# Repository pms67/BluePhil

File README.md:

# BluePhil
 STM32-based development board with various sensors. Update from LittleBrain board. Now includes GPS module, SD card, and CAN transceiver.

Gerber and assembly files ready for order at JLCPCB: https://jlcpcb.com/RPH

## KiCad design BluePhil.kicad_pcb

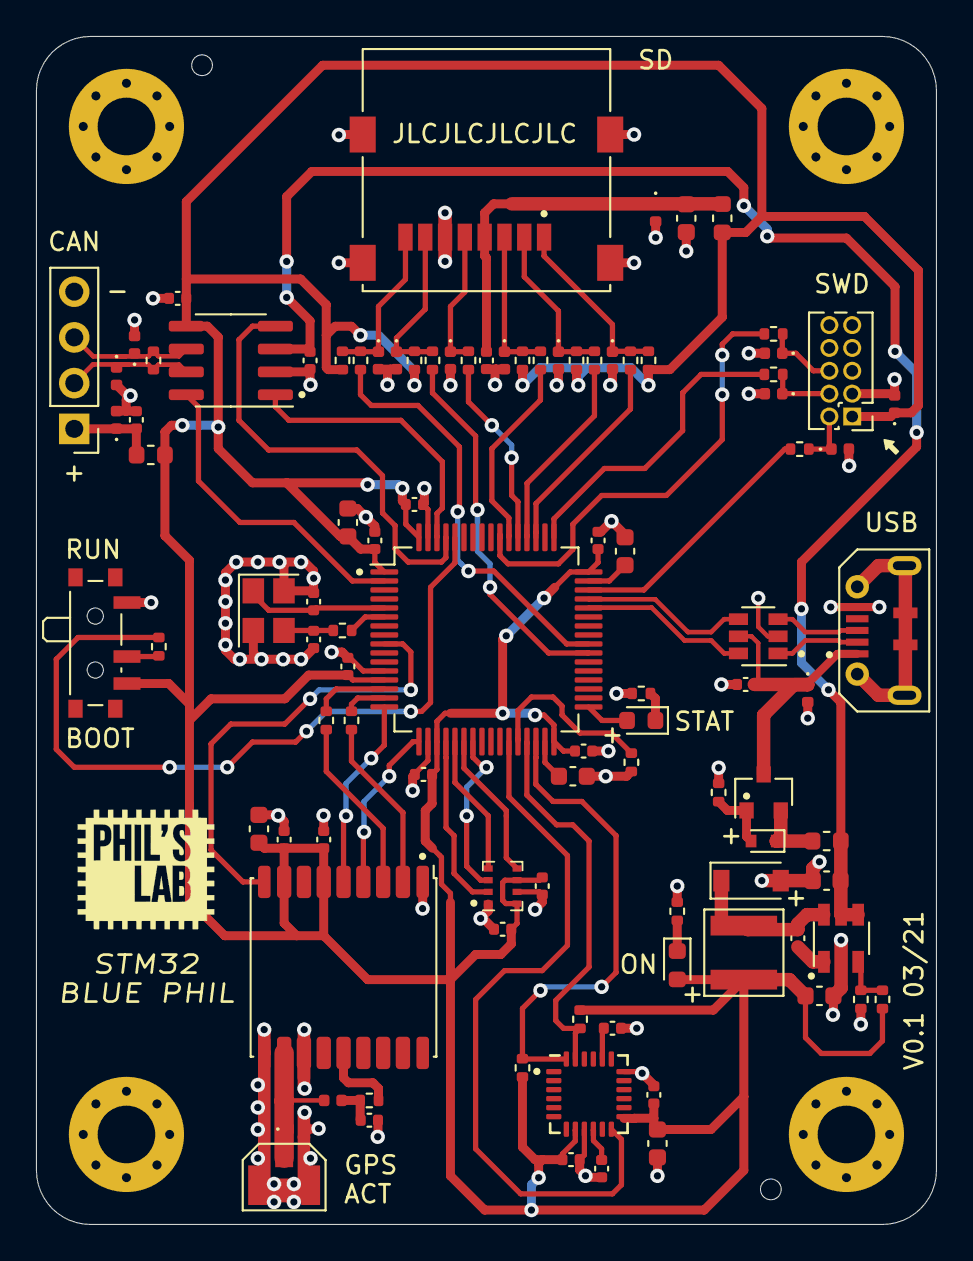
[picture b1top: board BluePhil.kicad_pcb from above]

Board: 2 copper layers, 50.0 x 66.0 mm, 103 parts (0 on the bottom side), 68 nets.

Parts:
C100, C207, C208: 2u2; C_0603_1608Metric
C101, C201, C202, C203, C204, C205, C206, C212, C301, C302, C400, C401, C403, C404, C405, C501, C502, C503, C504: 100n; C_0402_1005Metric
C102, C200, C300, C402, C500: 10u; C_0603_1608Metric
C209, C210: 10p; C_0402_1005Metric
C303: 10n; C_0402_1005Metric
C406: 2n2; C_0402_1005Metric
D100: LM5Z2V7T1G; D_SOD-523
D101: B5819W; D_SOD-123
D102: GREEN; LED_0603_1608Metric
D200: BLUE; LED_0603_1608Metric
D201, D202, D203, D204, D205, D300, D500, D501, D502, D503, D504, D505, D506, D507, D508, D509: RCLAMP0521P-N; D_0402_1005Metric
FB100, FB500, FB501: 100R; L_0603_1608Metric
H500, H501, H502, H503: MountingHole_Pad; MountingHole_3.2mm_M3_Pad_Via
J200: SWD; PinHeader_2x05_P1.27mm_Vertical
J201: USB_B_Micro; MicroXNJ
J300: U.FL; BWIPX-1-001E
J500: Micro_SD_Card; TF-102-15
J501: Conn_01x04; PinHeader_1x04_P2.54mm_Vertical
L1: 15u; MPIT4018-150M-LF
L300: 100n; L_0402_1005Metric
Q100: AO3401A; SOT-23
R100: 470R; R_0402_1005Metric
R101: 3k4; R_0402_1005Metric
R102: 1k02; R_0402_1005Metric
R103, R205: 1k; R_0402_1005Metric
R200, R202: 10k; R_0402_1005Metric
R201, R301, R302, R500, R501, R502, R503, R504, R505: 0R; R_0402_1005Metric
R203, R204: 2k2; R_0402_1005Metric
R206, R207, R208: 22R; R_0402_1005Metric
R300: 10R; R_0402_1005Metric
R506, R507, R508, R509, R510: 47k; R_0402_1005Metric
R511: 120R; R_0402_1005Metric
SW200: SW_SPDT; SW_SPDT_PCM12
U100: LM2842X; TSOT-23-6
U200: STM32F405RGT6; LQFP-64_10x10mm_P0.5mm
U201: USBLC6-2SC6; SOT-23-6
U300: MAX-M8Q; ublox_MAX
U400: SPL06-007; Bosch_LGA-8_2x2.5mm_P0.65mm_ClockwisePinNumbering
U401: MPU-6050; InvenSense_QFN-24_4x4mm_P0.5mm
U500: TJA1051T-3; SOIC-8_3.9x4.9mm_P1.27mm
Y200: 16MHz; Crystal_SMD_3225-4Pin_3.2x2.5mm

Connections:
+3V3: C102.1, C200.1, C201.1, C202.1, C203.1, C204.1, C205.1, C206.1, C300.1, C301.1, C302.1, C400.1, C401.1, C402.1, C403.1, C404.1, C503.2, D102.2, D201.1, FB500.2, FB501.2, J200.1, L1.2, R101.1, R203.1, R204.1, R506.1, R507.1, R508.1, R509.1, R510.1, SW200.3, U200.1, U200.13, U200.19, U200.32, U200.48, U200.64, U300.6, U300.8, U400.6, U400.8, U401.8, U401.13, U500.5
+5V: C100.1, C502.2, FB100.1, U100.4, U100.5, U500.3
/GPS/GPS_RX: R301.1, U300.3
/GPS/GPS_TX: R302.1, U300.2
/Microcontroller/CONN_SWCLK: D203.1, J200.4, R207.2
/Microcontroller/CONN_SWDIO: D204.1, J200.2, R206.2
/Microcontroller/CONN_SWO: D202.1, J200.6, R208.2
/Microcontroller/MCU_BOOT0: R200.1, U200.60
/Microcontroller/MCU_BOOT1: R202.1, U200.28
/Microcontroller/MCU_HSE_IN: C209.1, U200.5, Y200.1
/Microcontroller/MCU_HSE_OUT: R201.1, U200.6
/Microcontroller/MCU_HSE_OUT_R: C210.1, R201.2, Y200.3
/Microcontroller/MCU_LED_A: D200.2, U200.33
/Microcontroller/MCU_LED_K: D200.1, R205.1
/Microcontroller/MCU_VCAP1: C207.1, U200.31
/Microcontroller/MCU_VCAP2: C208.1, U200.47
/Microcontroller/SW_BOOT0: R200.2, SW200.2
/Miscellaneous/3V3_CAN: C504.1, D509.1, FB501.1, J501.1
/Miscellaneous/CAN+: D508.1, J501.2, R511.1, U500.7
/Miscellaneous/CAN-: D507.1, J501.3, R511.2, U500.6
/Miscellaneous/SD_CLK: D503.1, J500.5, R503.1
/Miscellaneous/SD_CMD: D502.1, J500.3, R502.1, R508.2
/Miscellaneous/SD_DAT0: D504.1, J500.7, R504.1, R507.2
/Miscellaneous/SD_DAT1: D505.1, J500.8, R505.1, R506.2
/Miscellaneous/SD_DAT2: D500.1, J500.1, R500.1, R510.2
/Miscellaneous/SD_DAT3: D501.1, J500.2, R501.1, R509.2
/Miscellaneous/SD_VDD: C500.2, C501.2, D506.1, FB500.1, J500.4
/Sensors/IMU_CPOUT: C406.1, U401.20
/Sensors/IMU_REGOUT: C405.1, U401.10
CAN_SILENT: U200.2, U500.8
CONN_USB_D+: J201.3, U201.3
CONN_USB_D-: J201.2, U201.1
GND: C100.2, C102.2, C200.2, C201.2, C202.2, C203.2, C204.2, C205.2, C206.2, C207.2, C208.2, C209.2, C210.2, C212.1, C300.2, C301.2, C302.2, C303.2, C400.2, C401.2, C402.2, C403.2, C404.2, C405.2, C406.2, C500.1, C501.1, C502.1, C503.1, C504.2, D101.2, D201.2, D202.2, D203.2, D204.2, D205.2, D300.2, D500.2, D501.2, D502.2, D503.2, D504.2, D505.2, D506.2, D507.2, D508.2, D509.2, H500.1, H501.1, H502.1, H503.1, J200.3, J200.5, J200.9, J201.5, J300.2, J500.6, J500.9, J501.4, R100.2, R102.2, R103.2, R202.2, R205.2, SW200.1, U100.2, U200.12, U200.18, U200.63, U201.2, U300.1, U300.10, U300.12, U400.1, U400.7, U401.9, U401.18, U500.2, Y200.2, Y200.4
GPS_NRST: U200.9, U300.9
GPS_ONOFF: U200.16, U300.5
GPS_PPS: U200.17, U300.4
IMU_INTERRUPT: U200.27, U401.12
MCU_CAN1_RX: U200.61, U500.4
MCU_CAN1_TX: U200.62, U500.1
MCU_I2C2_SCL: R203.2, U200.29, U401.23
MCU_I2C2_SDA: R204.2, U200.30, U401.24
MCU_SDIO_CK: R503.2, U200.53
MCU_SDIO_CMD: R502.2, U200.54
MCU_SDIO_D0: R504.2, U200.39
MCU_SDIO_D1: R505.2, U200.40
MCU_SDIO_D2: R500.2, U200.51
MCU_SDIO_D3: R501.2, U200.52
MCU_SPI1_MISO: U200.22, U400.5
MCU_SPI1_MOSI: U200.23, U400.3
MCU_SPI1_NSS: U200.20, U400.2
MCU_SPI1_SCK: U200.21, U400.4
MCU_SWCLK: R207.1, U200.49
MCU_SWDIO: R206.1, U200.46
MCU_SWO: R208.1, U200.55
MCU_UART4_RX: R302.2, U200.15
MCU_UART4_TX: R301.2, U200.14
MCU_USB_D+: U200.45, U201.4
MCU_USB_D-: U200.44, U201.6
unnamed: C101.1, D101.1, L1.1, U100.6
unnamed: C101.2, U100.1
unnamed: C303.1, L300.1, R300.1
unnamed: D100.1, FB100.2, Q100.2
unnamed: D100.2, Q100.1, R100.1
unnamed: D102.1, R103.1
unnamed: D300.1, J300.1, L300.2, U300.11
unnamed: R101.2, R102.1, U100.3
unnamed: R300.2, U300.14
VBUS: C212.2, D205.1, J201.1, Q100.3, U201.5

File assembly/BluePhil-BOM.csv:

Designator,Quantity,Value,Footprint,LCSC Part #
C102 C200 C300 C402 C500 ,5,10u,Capacitor_SMD:C_0603_1608Metric,C19702
C101 C201 C202 C203 C204 C205 C206 C212 C301 C302 C400 C401 C403 C404 C405 C501 C502 C503 C504 ,19,100n,Capacitor_SMD:C_0402_1005Metric,C1525
C100 C207 C208 ,3,2u2,Capacitor_SMD:C_0603_1608Metric,C23630
C209 C210 ,2,10p,Capacitor_SMD:C_0402_1005Metric,C32949
C303 ,1,10n,Capacitor_SMD:C_0402_1005Metric,C15195
C406 ,1,2n2,Capacitor_SMD:C_0402_1005Metric,C1531
D100 ,1,LM5Z2V7T1G,Diode_SMD:D_SOD-523,C131797
D101 ,1,B5819W,Diode_SMD:D_SOD-123,C8598
D102 ,1,GREEN,LED_SMD:LED_0603_1608Metric,C72043
D200 ,1,BLUE,LED_SMD:LED_0603_1608Metric,C72041
D201 D202 D203 D204 D205 D300 D500 D501 D502 D503 D504 D505 D506 D507 D508 D509 ,16,RCLAMP0521P-N,Diode_SMD:D_0402_1005Metric,C316043
FB100 FB500 FB501 ,3,100R,Inductor_SMD:L_0603_1608Metric,C1002
J200 ,1,SWD,Connector_PinHeader_1.27mm:PinHeader_2x05_P1.27mm_Vertical,C239059
J201 ,1,USB_B_Micro,BluePhil-Footprints:MicroXNJ,C404969
J300 ,1,U.FL,BluePhil-Footprints:BWIPX-1-001E,C496552
J500 ,1,Micro_SD_Card,BluePhil-Footprints:TF-102-15,C266609
L1 ,1,15u,BluePhil-Footprints:MPIT4018-150M-LF,C281265
L300 ,1,100n,Inductor_SMD:L_0402_1005Metric,C22726
Q100 ,1,AO3401A,Package_TO_SOT_SMD:SOT-23,C693260
R100 ,1,470R,Resistor_SMD:R_0402_1005Metric,C25117
R101 ,1,3k4,Resistor_SMD:R_0402_1005Metric,C4940
R102 ,1,1k02,Resistor_SMD:R_0402_1005Metric,C85373
R200 R202 ,2,10k,Resistor_SMD:R_0402_1005Metric,C25744
R201 R301 R302 R500 R501 R502 R503 R504 R505 ,9,0R,Resistor_SMD:R_0402_1005Metric,C17168
R203 R204 ,2,2k2,Resistor_SMD:R_0402_1005Metric,C25879
R103 R205 ,2,1k,Resistor_SMD:R_0402_1005Metric,C11702
R206 R207 R208 ,3,22R,Resistor_SMD:R_0402_1005Metric,C25092
R300 ,1,10R,Resistor_SMD:R_0402_1005Metric,C25077
R506 R507 R508 R509 R510 ,5,47k,Resistor_SMD:R_0402_1005Metric,C25792
R511 ,1,120R,Resistor_SMD:R_0402_1005Metric,C25079
SW200 ,1,SW_SPDT,Button_Switch_SMD:SW_SPDT_PCM12,C431541
U100 ,1,LM2842X,Package_TO_SOT_SMD:TSOT-23-6,C9403
U200 ,1,STM32F405RGT6,Package_QFP:LQFP-64_10x10mm_P0.5mm,C15742
U201 ,1,USBLC6-2SC6,Package_TO_SOT_SMD:SOT-23-6,C7519
U300 ,1,MAX-M8Q,RF_GPS:ublox_MAX,C90770
U400 ,1,SPL06-007,Package_LGA:Bosch_LGA-8_2x2.5mm_P0.65mm_ClockwisePinNumbering,C233787
U401 ,1,MPU-6050,Sensor_Motion:InvenSense_QFN-24_4x4mm_P0.5mm,C24112
U500 ,1,TJA1051T-3,Package_SO:SOIC-8_3.9x4.9mm_P1.27mm,C38695
Y200 ,1,16MHz,Crystal:Crystal_SMD_3225-4Pin_3.2x2.5mm, C13738
